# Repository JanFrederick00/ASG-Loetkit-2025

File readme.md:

# ASG-Loetkit-2025

[Löt-Video](https://www.youtube.com/watch?v=-um5J8tv-0Q)

[Demo-Video](https://www.youtube.com/watch?v=5mWFSo3QfBs)

Dieses Projekt ist eine kleine DMX-leuchte, die 9 LEDs enthält und individuell ansteuern kann.

Es wurde speziell dazu entwickelt, einen Einstieg in das SMD-Löten zu bieten. 
Dazu werden zwei der ICs vorgelötet, der Rest der Komponenten wurden dazu ausgewählt, so einfach wie möglich zu löten zu sein.

## Beschreibung der Schaltung

Das Herzstück des Gerätes ist der CH32V003 Microcontroller. 
Dieser empfängt DMX-Signale entweder von einem USB-Serial chip (FT232RL), oder von einem MAX485-Transciever, der die DMX-Signale übersetzt.
Über einen Schalter kann zwischen den beiden Signalquellen umgeschaltet werden. 

Der Microcontroller liest die gewünschte DMX-Adresse von dem DIP-Schalter aus, und entscheidet basierend auf dem eingestellten Kanal-Modus, welche RGB-Farbwerte die LEDs haben sollen.

Die LEDs sind vom Typ WS2812. Das sind einzeln steuerbare RGB-LEDs die häufig in PCs oder anderen bunt leuchtenden dingen verwendet werden. Alle LEDs werden seriell über einen einzigen Pin am 
Microcontroller angesteuert, und formen eine Kette wo das vorherige LED die Daten an die nächste weitergibt.

Der Microcontroller kann einen kleinen push-schalter auslesen, um durch die Modi durchzuwechseln. Eine kleine rote LED kann dazu verwendet werden um das Vorhandensein eines DMX-Signals zu zeigen.

## Verwendung

### Stromversorgung

Das Gerät wird über den USB-Port mit 5V Strom versorgt. 

### DMX-Signal

Als Signalquelle stehen zwei Möglichkeiten zur Auswahl:

- DMX: Die beiden 3-pin Steckverbinder oben rechts sind die DMX in / out ports. Sie verhalten sich wie die Üblichen 3-pin XLR-buchsen, sind aber kleiner und günstiger. Der Schalter muss dafür in der rechten Stellung sein.
- USB: Wenn der FT232-chip installiert ist, dann kann das Gerät auch an einen Computer direkt angeschlossen werden. Dafür verwenden wir die Software `QLC+`, die diesen Chip nativ unterstützt. Der Schalter muss dafür in der linken Stellung sein.

**Anzeigen des DMX-Signals:**

Wenn der Push-schalter gedrückt ist wärend das Gerät eingesteckt wird, dann blinkt die rote LED D10 kurz, wenn ein neues DMX-Datenpaket empfangen wurde. 

### Auswahl eines Kanal-Moduses

Über einen Klick des Push-schalters wird durch die Kanal-Modi gewechselt. Standardmäßig ist das Gerät im 4-Kanal-Modus. Solange der Knopf gedrückt ist wird ein Muster auf den LEDs gezeigt, der den Modus symbolisiert. 

Die verfügbaren Modi sind wie folgt:

**4-Kanal-Modus**

Klassisches RGB + Dimmer

|Channel|Function|
|-------|--------|
|1|R|
|2|G|
|3|B|
|4|Dimmer|

**27-Kanal-Modus**

R, G, B für jede der 9 LEDs

|Channel|Function|
|-------|--------|
|3*n+1|R für Dn|
|3*n+2|G für Dn|
|3*n+3|B für Dn|

(wobei n = 0-8 für die 9 LEDs)

**28-Kanal-Modus**

R, G, B für jede der 9 LEDs, und ein Dimmer der alle gleichzeitig dimmt.

|Channel|Function|
|-------|--------|
|1|Dimmer|
|3*n+2|R für Dn|
|3*n+3|G für Dn|
|3*n+4|B für Dn|

(wobei n = 0-8 für die 9 LEDs)

**36-Kanal-Modus**

R, G, B und Dimmer für jede der 9 LEDs

|Channel|Function|
|-------|--------|
|4*n+1|R für Dn|
|4*n+2|G für Dn|
|4*n+3|B für Dn|
|4*n+4|Dimmer für Dn|

**HSV-Modus**

3 Kanäle, die Farbe wird dabei im [HSV-Farbraum](https://de.wikipedia.org/wiki/HSV-Farbraum) eingestellt. Kanal 3 ist dabei Helligkeit, die wie der Dimmer agiert.

|Channel|Function|
|-------|--------|
|1|Hue (Farbton)|
|2|Saturation (Sättigung)|
|3|Value (Dimmer)|

**3-Kanal-Modus**

Klassisches RGB

|Channel|Function|
|-------|--------|
|1|R|
|2|G|
|3|B|

### Demo-Modus

Wenn man den Auswahlknopf mehr als 10 sekunden hält, dann wechselt das Gerät in einen eingebauten Demo-Modus.
Alle eingehenden DMX-Signale werden dabei ignoriert.

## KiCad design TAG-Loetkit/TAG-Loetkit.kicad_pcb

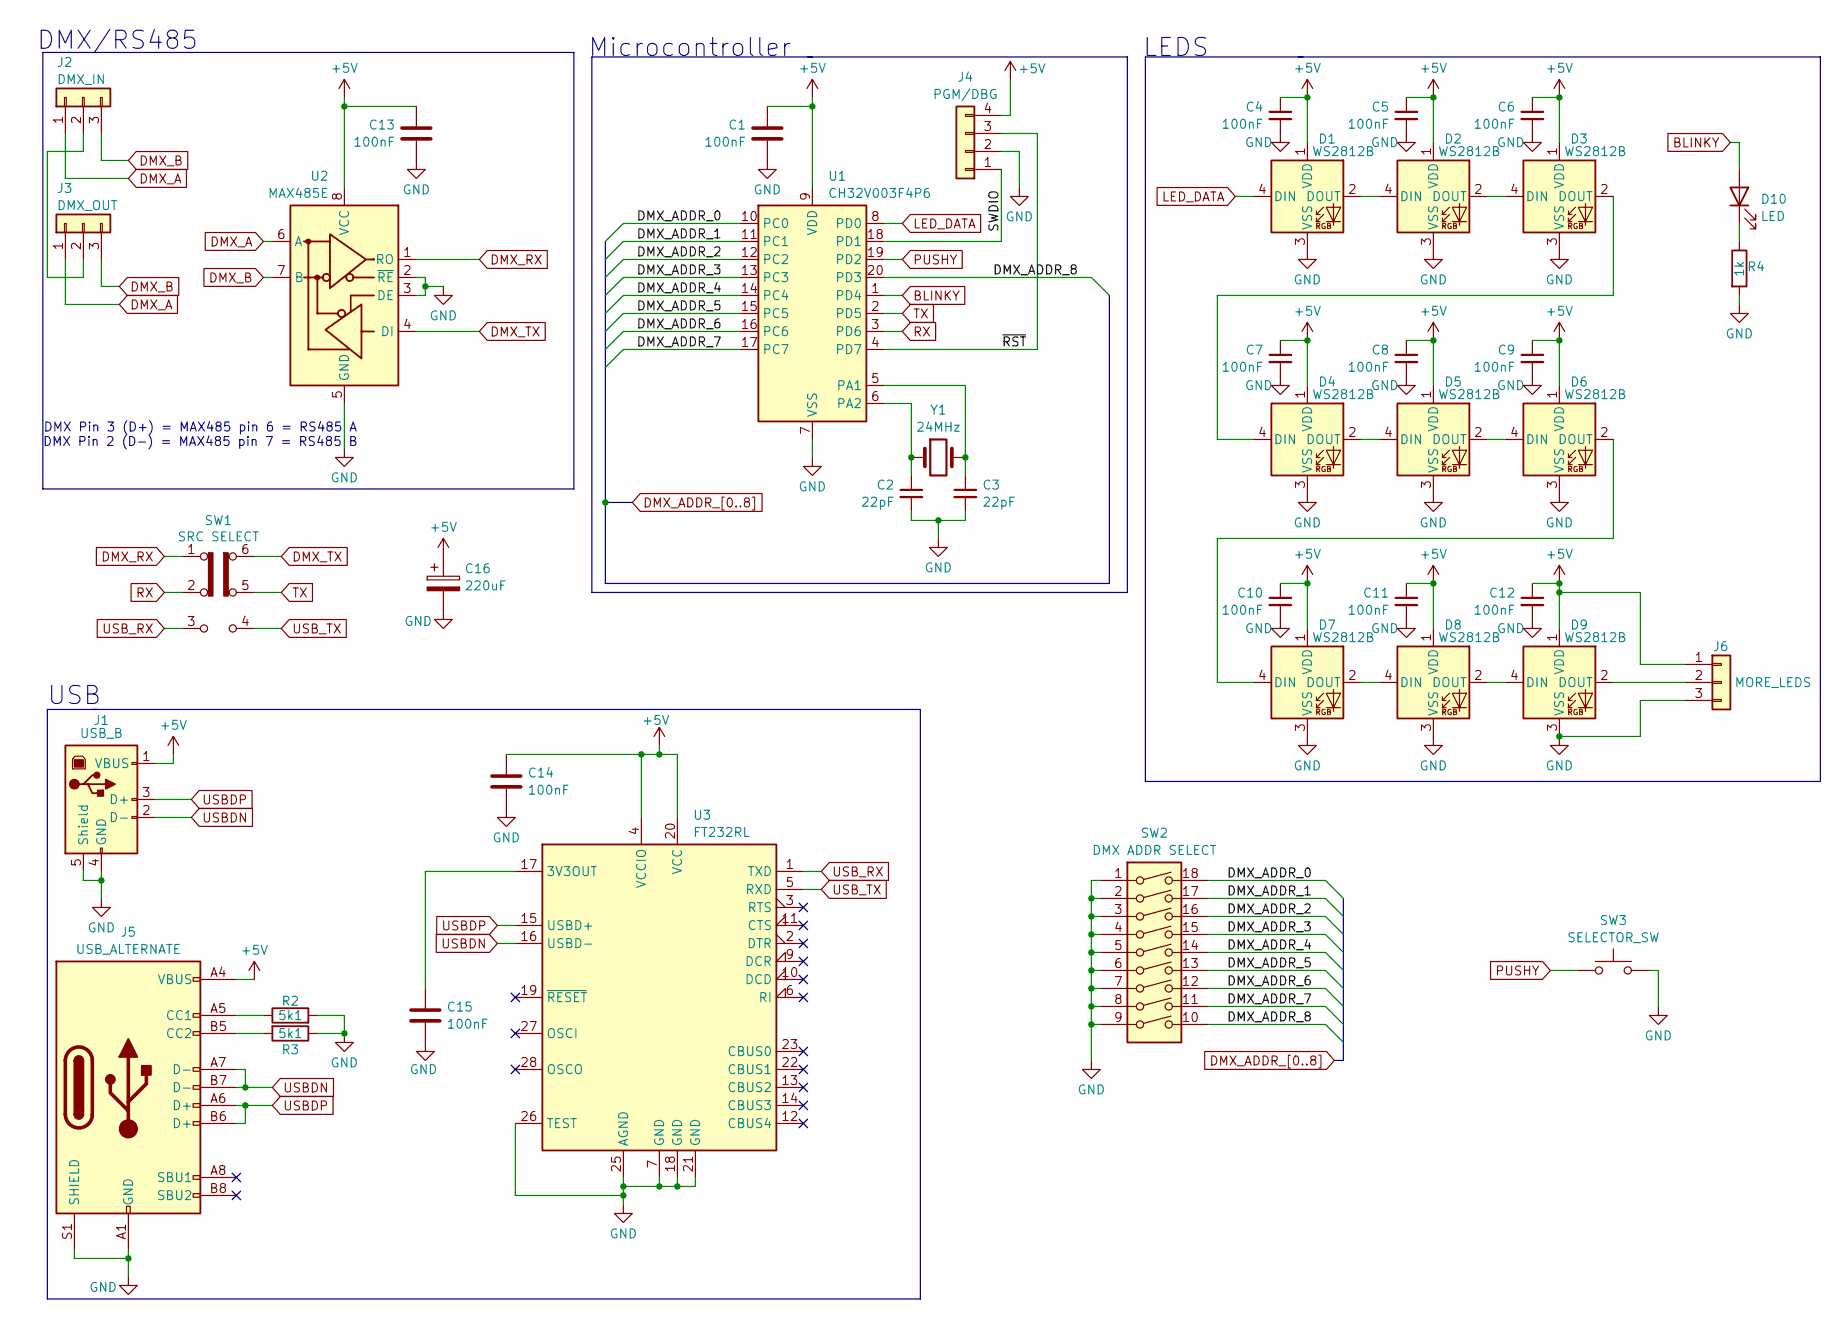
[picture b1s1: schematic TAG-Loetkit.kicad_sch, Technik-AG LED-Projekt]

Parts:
C1: 100nF; C_0805_2012Metric_Pad1.18x1.45mm_HandSolder
C2, C3: 22pF; C_1206_3216Metric_Pad1.33x1.80mm_HandSolder
C4, C5, C6, C7, C8, C9, C10, C11, C12, C13, C14, C15: 100nF; C_1206_3216Metric_Pad1.33x1.80mm_HandSolder
C16: 220uF; CP_Radial_D6.3mm_P2.50mm
D1, D2, D3, D4, D5, D6, D7, D8, D9: WS2812B; LED_WS2812B_PLCC4_5.0x5.0mm_P3.2mm_XLPads
D10: LED; LED_1206_3216Metric_Pad1.42x1.75mm_HandSolder
J1: USB_B; USB_B_Lumberg_2411_02_Horizontal
J2: DMX_IN; JST_XH_B3B-XH-A_1x03_P2.50mm_Vertical
J3: DMX_OUT; JST_XH_B3B-XH-A_1x03_P2.50mm_Vertical
J4: PGM/DBG; PinHeader_1x04_P2.54mm_Vertical
J5: USB_ALTERNATE; Korean_USBC
J6: MORE_LEDS; PinHeader_1x03_P2.54mm_Vertical
R2, R3: 5k1; R_0805_2012Metric_Pad1.20x1.40mm_HandSolder
R4: 1k; R_1206_3216Metric_Pad1.30x1.75mm_HandSolder
SW1: SRC SELECT; HanElectricDPDTSlideSwitch
SW2: DMX ADDR SELECT; SW_DIP_SPSTx09_Slide_9.78x25.04mm_W7.62mm_P2.54mm
SW3: SELECTOR_SW; SW_PUSH_6mm
U1: CH32V003F4P6; TSSOP-20_4.4x6.5mm_P0.65mm
U2: MAX485E; SOIC-8_3.9x4.9mm_P1.27mm
U3: FT232RL; SSOP-28_5.3x10.2mm_P0.65mm
Y1: 24MHz; Crystal_HC50_Vertical

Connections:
+5V: C1.1, C4.1, C5.1, C6.1, C7.1, C8.1, C9.1, C10.1, C11.1, C12.1, C13.1, C14.1, C16.1, D1.1 (VDD), D2.1 (VDD), D3.1 (VDD), D4.1 (VDD), D5.1 (VDD), D6.1 (VDD), D7.1 (VDD), D8.1 (VDD), D9.1 (VDD), J1.1 (VBUS), J4.4, J5.A4 (VBUS), J5.A9 (VBUS), J5.B4 (VBUS), J5.B9 (VBUS), J6.1, U1.9 (VDD), U2.8 (VCC), U3.4 (VCCIO), U3.20 (VCC)
/SWDIO: J4.1, U1.18 (PD1)
/~RST: J4.3, U1.4 (PD7)
BLINKY: D10.2 (A), U1.1 (PD4)
DMX_A: J2.1, J3.1, U2.6 (A)
DMX_ADDR_0: SW2.18, U1.10 (PC0)
DMX_ADDR_1: SW2.17, U1.11 (PC1)
DMX_ADDR_2: SW2.16, U1.12 (PC2)
DMX_ADDR_3: SW2.15, U1.13 (PC3)
DMX_ADDR_4: SW2.14, U1.14 (PC4)
DMX_ADDR_5: SW2.13, U1.15 (PC5)
DMX_ADDR_6: SW2.12, U1.16 (PC6)
DMX_ADDR_7: SW2.11, U1.17 (PC7)
DMX_ADDR_8: SW2.10, U1.20 (PD3)
DMX_B: J2.3, J3.3, U2.7 (B)
DMX_RX: SW1.1 (A), U2.1 (RO)
DMX_TX: SW1.6 (C), U2.4 (DI)
GND: C1.2, C2.2, C3.2, C4.2, C5.2, C6.2, C7.2, C8.2, C9.2, C10.2, C11.2, C12.2, C13.2, C14.2, C15.2, C16.2, D1.3 (VSS), D2.3 (VSS), D3.3 (VSS), D4.3 (VSS), D5.3 (VSS), D6.3 (VSS), D7.3 (VSS), D8.3 (VSS), D9.3 (VSS), J1.4 (GND), J1.5 (Shield), J4.2, J5.A1 (GND), J5.A12 (GND), J5.B1 (GND), J5.B12 (GND), J5.S1 (SHIELD), J6.3, R2.2, R3.1, R4.2, SW2.1, SW2.2, SW2.3, SW2.4, SW2.5, SW2.6, SW2.7, SW2.8, SW2.9, SW3.2, U1.7 (VSS), U2.2 (~RE), U2.3 (DE), U2.5 (GND), U3.7 (GND), U3.18 (GND), U3.21 (GND), U3.25 (AGND), U3.26 (TEST)
LED_DATA: D1.4 (DIN), U1.8 (PD0)
unnamed: D1.2 (DOUT), D2.4 (DIN)
unnamed: D2.2 (DOUT), D3.4 (DIN)
unnamed: D3.2 (DOUT), D4.4 (DIN)
unnamed: D4.2 (DOUT), D5.4 (DIN)
unnamed: D5.2 (DOUT), D6.4 (DIN)
unnamed: D6.2 (DOUT), D7.4 (DIN)
unnamed: D7.2 (DOUT), D8.4 (DIN)
unnamed: D8.2 (DOUT), D9.4 (DIN)
unnamed: D9.2 (DOUT), J6.2
unnamed: D10.1 (K), R4.1
unnamed: J2.2, J3.2
unnamed: J5.A5 (CC1), R2.1
unnamed: J5.B5 (CC2), R3.2
unnamed: C3.1, U1.5 (PA1), Y1.2
unnamed: C2.1, U1.6 (PA2), Y1.1
unnamed: C15.1, U3.17 (3V3OUT)
PUSHY: SW3.1, U1.19 (PD2)
RX: SW1.2 (B), U1.3 (PD6)
TX: SW1.5 (B), U1.2 (PD5)
USBDN: J1.2 (D-), J5.A7 (D-), J5.B7 (D-), U3.16 (USBD-)
USBDP: J1.3 (D+), J5.A6 (D+), J5.B6 (D+), U3.15 (USBD+)
USB_RX: SW1.3 (C), U3.1 (TXD)
USB_TX: SW1.4 (A), U3.5 (RXD)

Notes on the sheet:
DMX/RS485
LEDS
USB
Microcontroller
DMX Pin 3 (D+) = MAX485 pin 6 = RS485 A DMX Pin 2 (D-) = MAX485 pin 7 = RS485 B

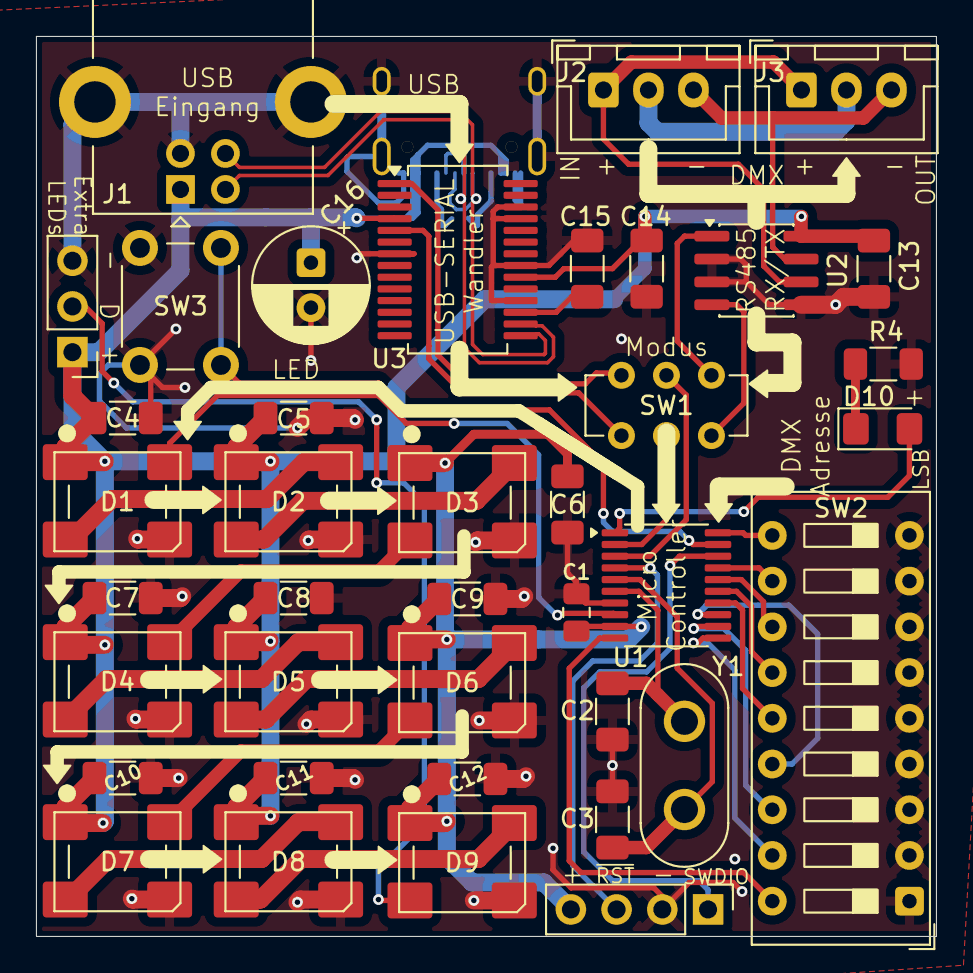
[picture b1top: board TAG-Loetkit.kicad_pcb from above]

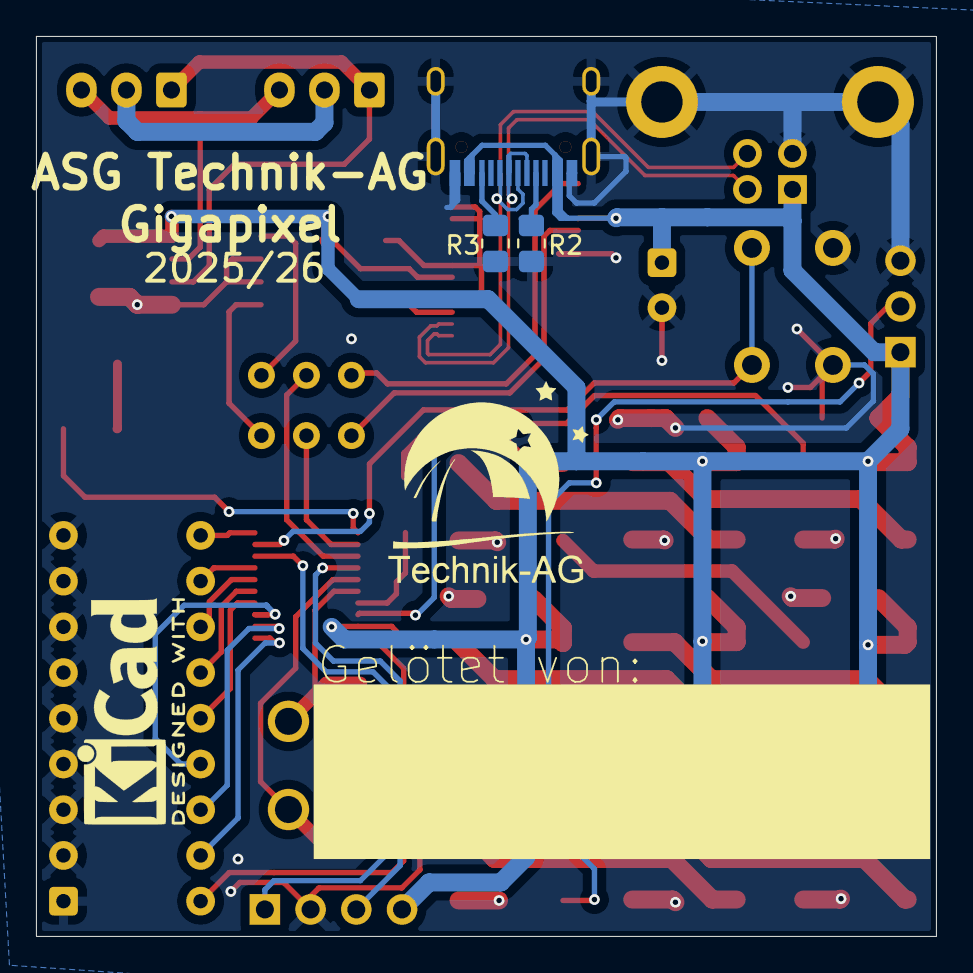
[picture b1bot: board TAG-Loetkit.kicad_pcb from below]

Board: 2 copper layers, 50.0 x 50.0 mm, 42 parts (3 on the bottom side), 42 nets.

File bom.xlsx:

Reference | Beschreibung | Wer Lötet? | Link | Kosten/stück | Anzahl | MOQ | Margin | Anzahl benötigt insgesamt | Anzahl (aufgerundet) | Kosten
C1 | Kondensator 100nF 0805 | Freddy | (Stock Freddy) | 0 | 1 | 1 | 0 | 15 | 15 | 0
U1 | Microcontroller CH32V003F4P6 | Freddy | (Stock Freddy) | 0.23 | 1 | 1 | 0 | 15 | 15 | 3.45
U3 | FT232RL | Freddy | (Stock Freddy) | 0 | 1 | 1 | 0 | 15 | 15 | 0
C4, C5, C6, C7, C8, C9, C10, C11, C12, C13, C14, C15 | Kondensator 100nF 1206 | Schüler | https://www.lcsc.com/product-detail/C82601.html | 9.2999999999999992E-3 | 12 | 50 | 4 | 240 | 250 | 2.3249999999999997
U2 | MAX485 | Schüler | https://www.lcsc.com/product-detail/C42428254.html?s_z=n_max485 | 9.0399999999999994E-2 | 1 | 5 | 0 | 15 | 15 | 1.3559999999999999
C2, C3 | Kondensator 22pF 1206 | Schüler | https://www.lcsc.com/product-detail/C377027.html | 8.6999999999999994E-3 | 2 | 50 | 1 | 45 | 50 | 0.43499999999999994
D10 | LED rot 1206 | Schüler | https://www.lcsc.com/product-detail/C3646938.html | 1.0500000000000001E-2 | 1 | 50 | 1 | 30 | 50 | 0.52500000000000002
D1, D2, D3, D4, D5, D6, D7, D8, D9 | RGB-LED WS2812 | Schüler | https://www.lcsc.com/product-detail/C22461793.html?s_z=n_ws2812 | 2.1100000000000001E-2 | 9 | 20 | 0 | 135 | 140 | 2.9540000000000002
Y1 | Quartz 24MHz | Schüler | https://www.lcsc.com/product-detail/C7275046.html | 4.6100000000000002E-2 | 1 | 10 | 0 | 15 | 20 | 0.92200000000000004
C16 | Kondensator Elko THT 220uF 5.0x2.5 | Schüler | (Stock Freddy) | 0 | 1 | 1 | 0 | 15 | 15 | 0
SW1 | Slide Switch DPDT | Schüler | https://www.lcsc.com/product-detail/C22435668.html?s_z=n_dpdt | 3.7199999999999997E-2 | 1 | 10 | 0 | 15 | 20 | 0.74399999999999999
SW2 | DIP-Schalter 9P | Schüler | https://www.lcsc.com/product-detail/C3024975.html | 0.27510000000000001 | 1 | 19 | 0 | 15 | 19 | 5.2269000000000005
SW3 | Tactile Pushbutton | Schüler | https://www.lcsc.com/product-detail/C42416244.html | 1.49E-2 | 1 | 50 | 0 | 15 | 50 | 0.745
J1 | USB B | Schüler | https://www.lcsc.com/product-detail/C2962393.html | 8.6099999999999996E-2 | 1 | 5 | 0 | 15 | 15 | 1.2914999999999999
J2, J3 | JST-XH 3P | Schüler | https://www.lcsc.com/product-detail/C5160912.html | 8.3000000000000001E-3 | 2 | 50 | 0 | 30 | 50 | 0.41499999999999998
 | Platinen | N/A |  | 0.39 | 1 | 20 | 0 | 15 | 20 | 7.8000000000000007
Anzahl Platinen: |  | 15
 |  |  |  |  |  |  |  |  |  | 28.189399999999999

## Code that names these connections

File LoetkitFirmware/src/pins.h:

#pragma once
#include <Arduino.h>

const uint8_t BUILTIN_LED = PD4;
const uint8_t PIN_PUSHBUTTON = PD2;
const uint8_t NUM_CONFIG_BITS = 9;
const uint8_t CONFIG_SWITCH_PINS[NUM_CONFIG_BITS] = {PD3, PC7, PC6, PC5, PC4, PC3, PC2, PC1, PC0}; // LSB first

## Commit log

2025-10-24 erste Version
2025-10-25 Quellcode für Firmware hinzugefügt
2025-10-25 Datenblätter hinzugefügt
2025-10-25 Dateien entfernt
2025-11-14 Firmware finalisiert
2025-11-15 Dokumentation
2025-11-16 Mehr Doku
2026-03-14 Anleitung-pdf
